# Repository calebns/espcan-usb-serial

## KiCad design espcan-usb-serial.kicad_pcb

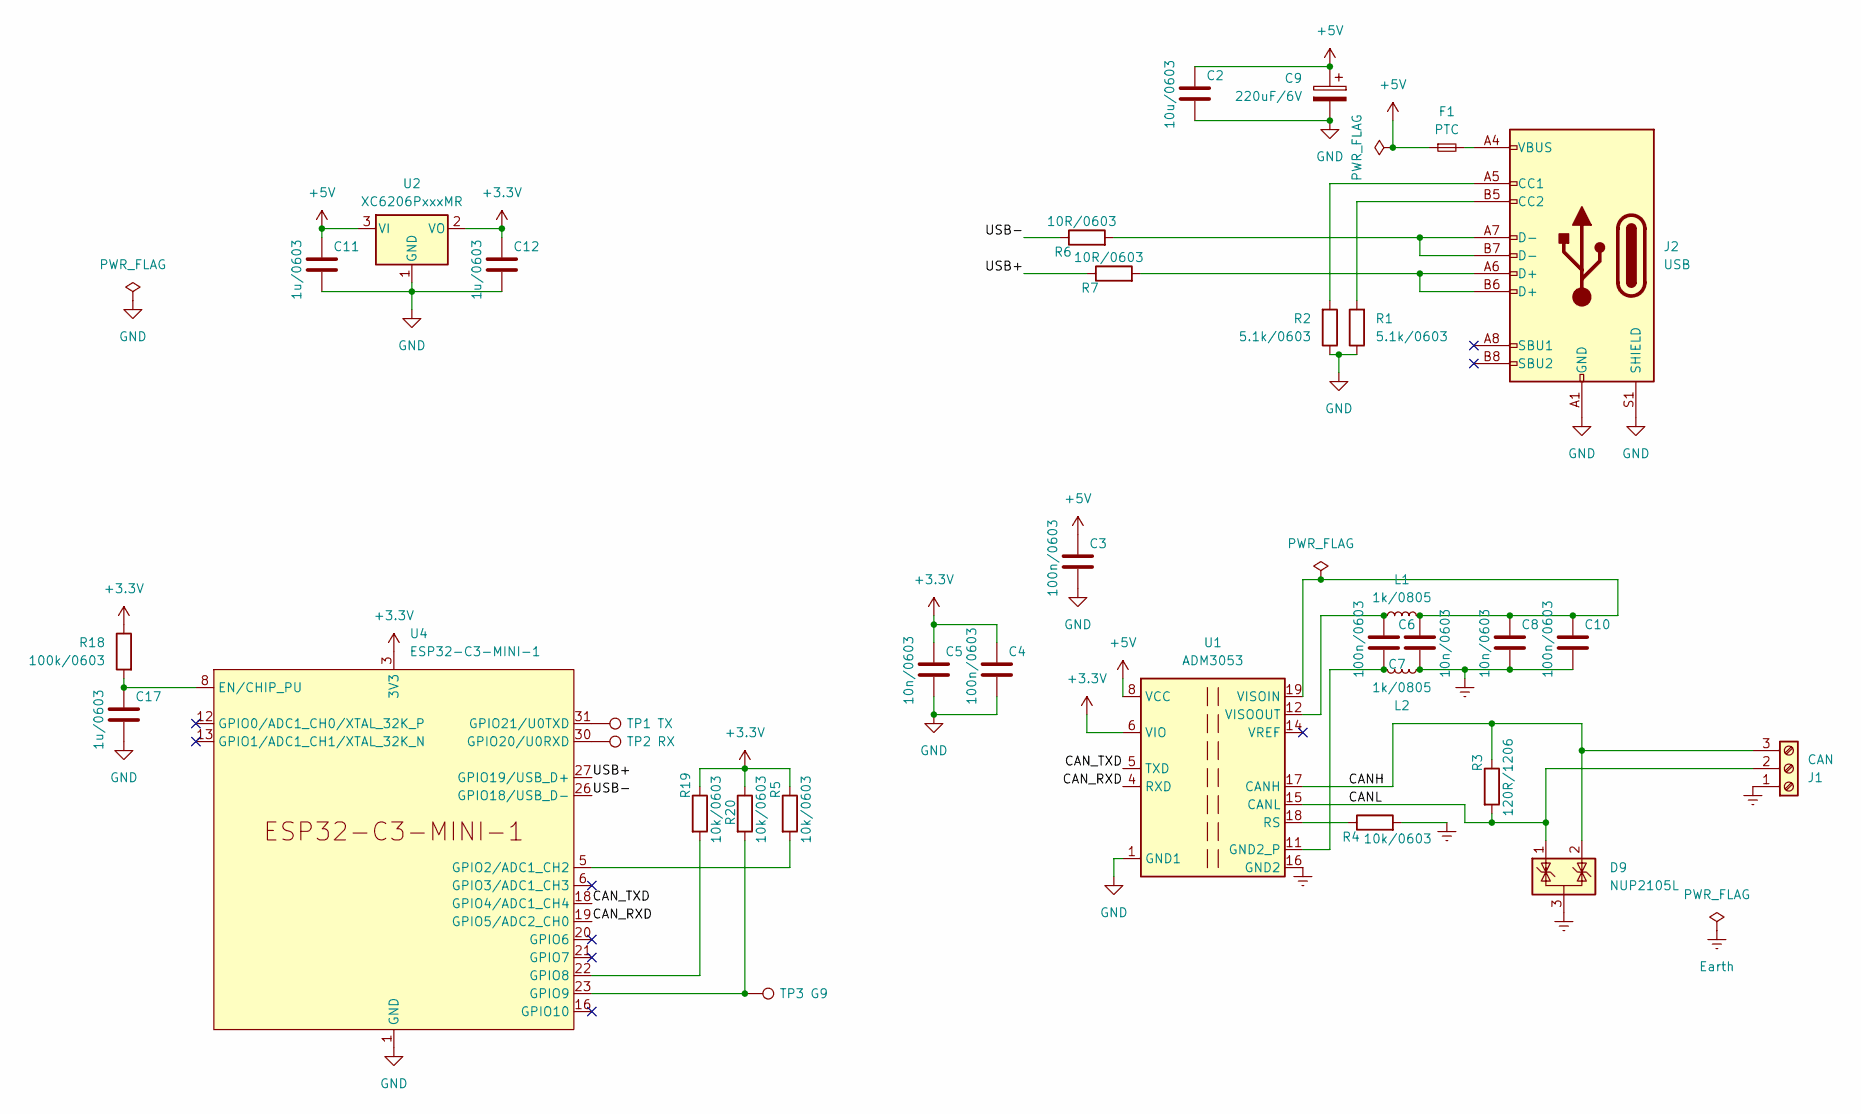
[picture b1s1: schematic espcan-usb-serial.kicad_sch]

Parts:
C2: 10u/0603; C_0603_1608Metric
C3, C4, C7, C10: 100n/0603; C_0603_1608Metric
C5, C6, C8: 10n/0603; C_0603_1608Metric
C9: 220uF/6V; CP_EIA-3528-15_AVX-H
C11, C12, C17: 1u/0603; C_0603_1608Metric
D9: NUP2105L; SOT-23
F1: PTC; R_1206_3216Metric
J1: CAN; TerminalBlock_Phoenix_MKDS-3-3-5.08_1x03_P5.08mm_Horizontal
J2: USB; USB_C_Receptacle_HRO_TYPE-C-31-M-12
L1, L2: 1k/0805; R_0805_2012Metric
R1, R2: 5.1k/0603; R_0603_1608Metric
R3: 120R/1206; R_1206_3216Metric
R4, R5, R19, R20: 10k/0603; R_0603_1608Metric
R6, R7: 10R/0603; R_0603_1608Metric
R18: 100k/0603; R_0603_1608Metric
TP1: TX; TestPoint_Pad_D1.0mm
TP2: RX; TestPoint_Pad_D1.0mm
TP3: G9; TestPoint_Pad_D1.0mm
U1: ADM3053; SOIC-20W_7.5x12.8mm_P1.27mm
U2: XC6206PxxxMR; SOT-23-3
U4: ESP32-C3-MINI-1; ESP32-C3-MINI-1U

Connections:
+3.3V: C4.1, C5.1, C12.1, R5.1, R18.1, R19.1, R20.1, U1.6 (VIO), U2.2 (VO), U4.3 (3V3)
+5V: C2.1, C3.1, C9.1, C11.1, F1.1, U1.8 (VCC), U2.3 (VI)
/CANH: D9.2 (K), J1.3, R3.1, U1.17 (CANH)
/CANL: D9.1 (K), J1.2, R3.2, U1.15 (CANL)
/CAN_RXD: U1.4 (RXD), U4.19 (GPIO5/ADC2_CH0)
/CAN_TXD: U1.5 (TXD), U4.18 (GPIO4/ADC1_CH4)
/USB+: R7.1, U4.27 (GPIO19/USB_D+)
/USB-: R6.1, U4.26 (GPIO18/USB_D-)
Earth: C6.2, C8.2, C10.2, D9.3 (A), J1.1, L2.2, R4.2, U1.16 (GND2), U1.20 (GND2)
GND: C2.2, C3.2, C4.2, C5.2, C9.2, C11.2, C12.2, C17.2, J2.A1 (GND), J2.A12 (GND), J2.B1 (GND), J2.B12 (GND), J2.S1 (SHIELD), R1.1, R2.1, U1.1 (GND1), U1.3 (GND1), U1.7 (GND1), U1.9 (GND1), U1.10 (GND1), U2.1 (GND), U4.1 (GND), U4.2 (GND), U4.11 (GND), U4.14 (GND), U4.36 (GND), U4.37 (GND), U4.38 (GND), U4.39 (GND), U4.40 (GND), U4.41 (GND), U4.42 (GND), U4.43 (GND), U4.44 (GND), U4.45 (GND), U4.46 (GND), U4.47 (GND), U4.48 (GND), U4.49 (GND), U4.50 (GND), U4.51 (GND), U4.52 (GND), U4.53 (GND)
unnamed: C7.2, L2.1, U1.11 (GND2_P), U1.13 (GND2_P)
unnamed: F1.2, J2.A4 (VBUS), J2.A9 (VBUS), J2.B4 (VBUS), J2.B9 (VBUS)
unnamed: J2.A5 (CC1), R2.2
unnamed: J2.B5 (CC2), R1.2
unnamed: J2.A6 (D+), J2.B6 (D+), R7.2
unnamed: J2.A7 (D-), J2.B7 (D-), R6.2
unnamed: R4.1, U1.18 (RS)
unnamed: C6.1, C8.1, C10.1, L1.2, U1.19 (VISOIN)
unnamed: C7.1, L1.1, U1.12 (VISOOUT)
unnamed: C17.1, R18.2, U4.8 (EN/CHIP_PU)
unnamed: R5.2, U4.5 (GPIO2/ADC1_CH2)
unnamed: R19.2, U4.22 (GPIO8)
unnamed: R20.2, TP3.1, U4.23 (GPIO9)
unnamed: TP2.1, U4.30 (GPIO20/U0RXD)
unnamed: TP1.1, U4.31 (GPIO21/U0TXD)

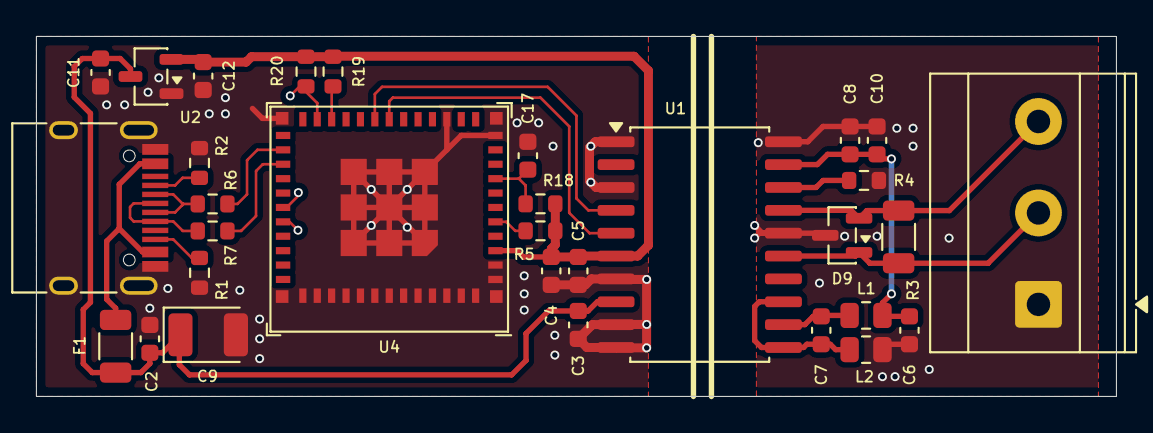
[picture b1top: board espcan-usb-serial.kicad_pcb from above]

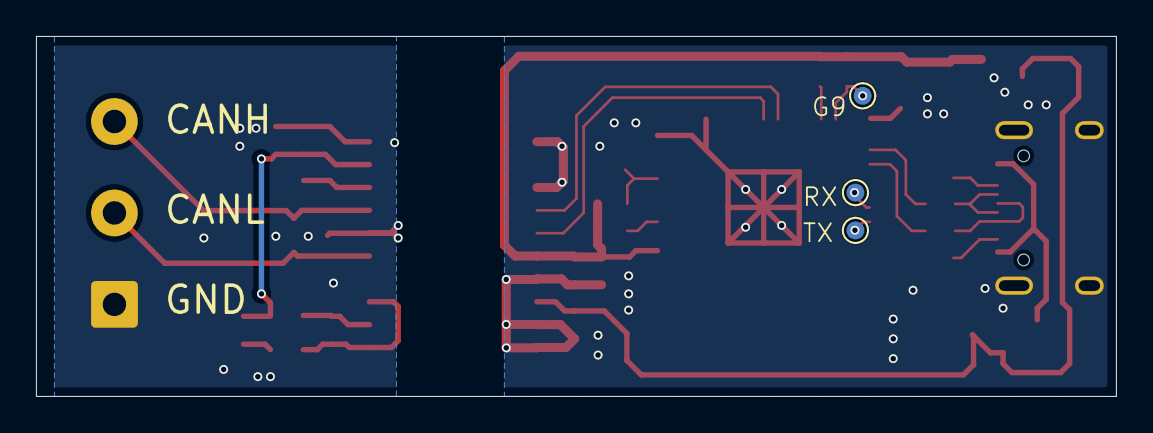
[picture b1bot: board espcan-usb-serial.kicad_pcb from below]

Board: 2 copper layers, 60.0 x 20.0 mm, 34 parts (3 on the bottom side), 25 nets.

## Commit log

2025-12-23 rev1 ready
2026-01-11 rev1 add firmware binary
    FW is built with a custom patch to esphome!!
